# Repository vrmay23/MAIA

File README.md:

# MAIA
ADAS for blind dogs!

## Third-Party Dependencies

This project uses the VL53L5CX Ultra Lite Driver (ULD) from
STMicroelectronics, licensed under BSD-3-Clause.

The ULD is NOT included in this repository. It is downloaded
automatically at build time via the ESP-IDF Component Manager
using the manifest at `components/drivers/vl53l5cx/idf_component.yml`.

- Source: https://github.com/STMicroelectronics/stm32-vl53l5cx
- License: BSD-3-Clause, (c) STMicroelectronics

### Integration approach

The ST ULD provides the sensor core logic (`vl53l5cx_api.c`)
and expects the user to implement a platform layer (`platform.h`)
with I2C and delay callbacks.

MAIA provides its own `platform.h` and `vl53l5cx_platform.c`
using the ESP-IDF v6.0 new I2C master API. The ST `porting/`
directory is intentionally excluded from the build — only
`modules/vl53l5cx_api.c` is compiled from the ULD.

This keeps the repository 100% Apache 2.0 while the ST ULD
is consumed as an external dependency at build time.

## Building
idf.py build

The Component Manager downloads the ST ULD automatically.
No manual steps required.

## ⚠️ DISCLAIMER

THIS IS AN EXPERIMENTAL OPEN-SOURCE PROJECT FOR EDUCATIONAL
AND RESEARCH PURPOSES ONLY.

No Warranty of Operation: This ADAS system for blind dogs is
provided on an "AS IS" BASIS, without warranties or conditions
of any kind, either express or implied. ToF sensors are subject
to environmental interference, signal noise, blind spots, and
false negatives/positives.

Assumption of Risk: The use of this hardware and firmware on
animals is at the sole discretion and risk of the user/builder.
The author(s) shall not be held liable for any collisions,
injuries, property damage, or any other incidents resulting
from the use or failure of this device.

Not a Medical or Safety Device: This project is NOT a certified
medical or assistive device. It is not a substitute for human
supervision, professional veterinary advice, or proper
orientation training for visually impaired animals.

Hardware Safety: The builder is responsible for ensuring
electrical safety (battery insulation, thermal management) and
mechanical integrity (secure attachment to the animal) to
prevent risks of shock, fire, or physical harm.

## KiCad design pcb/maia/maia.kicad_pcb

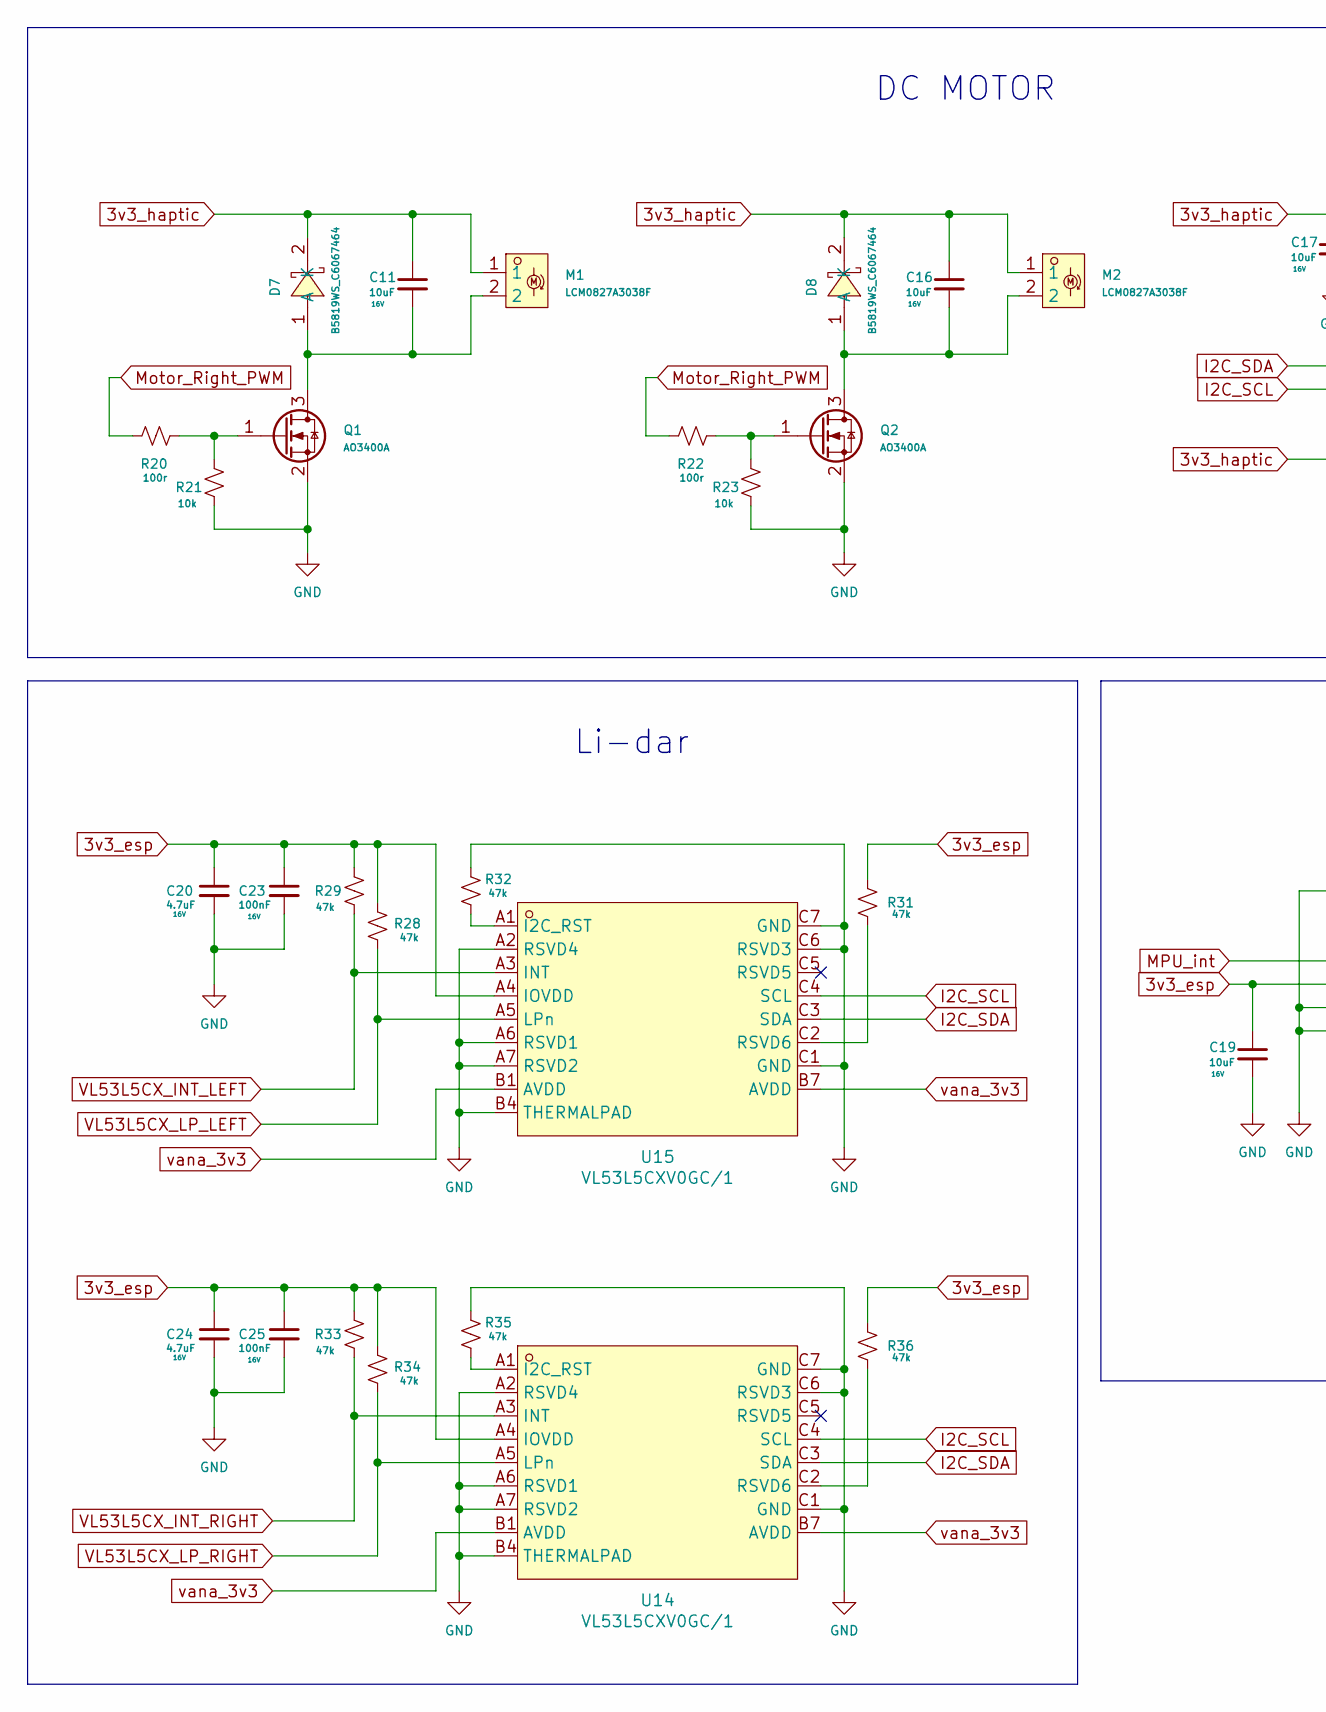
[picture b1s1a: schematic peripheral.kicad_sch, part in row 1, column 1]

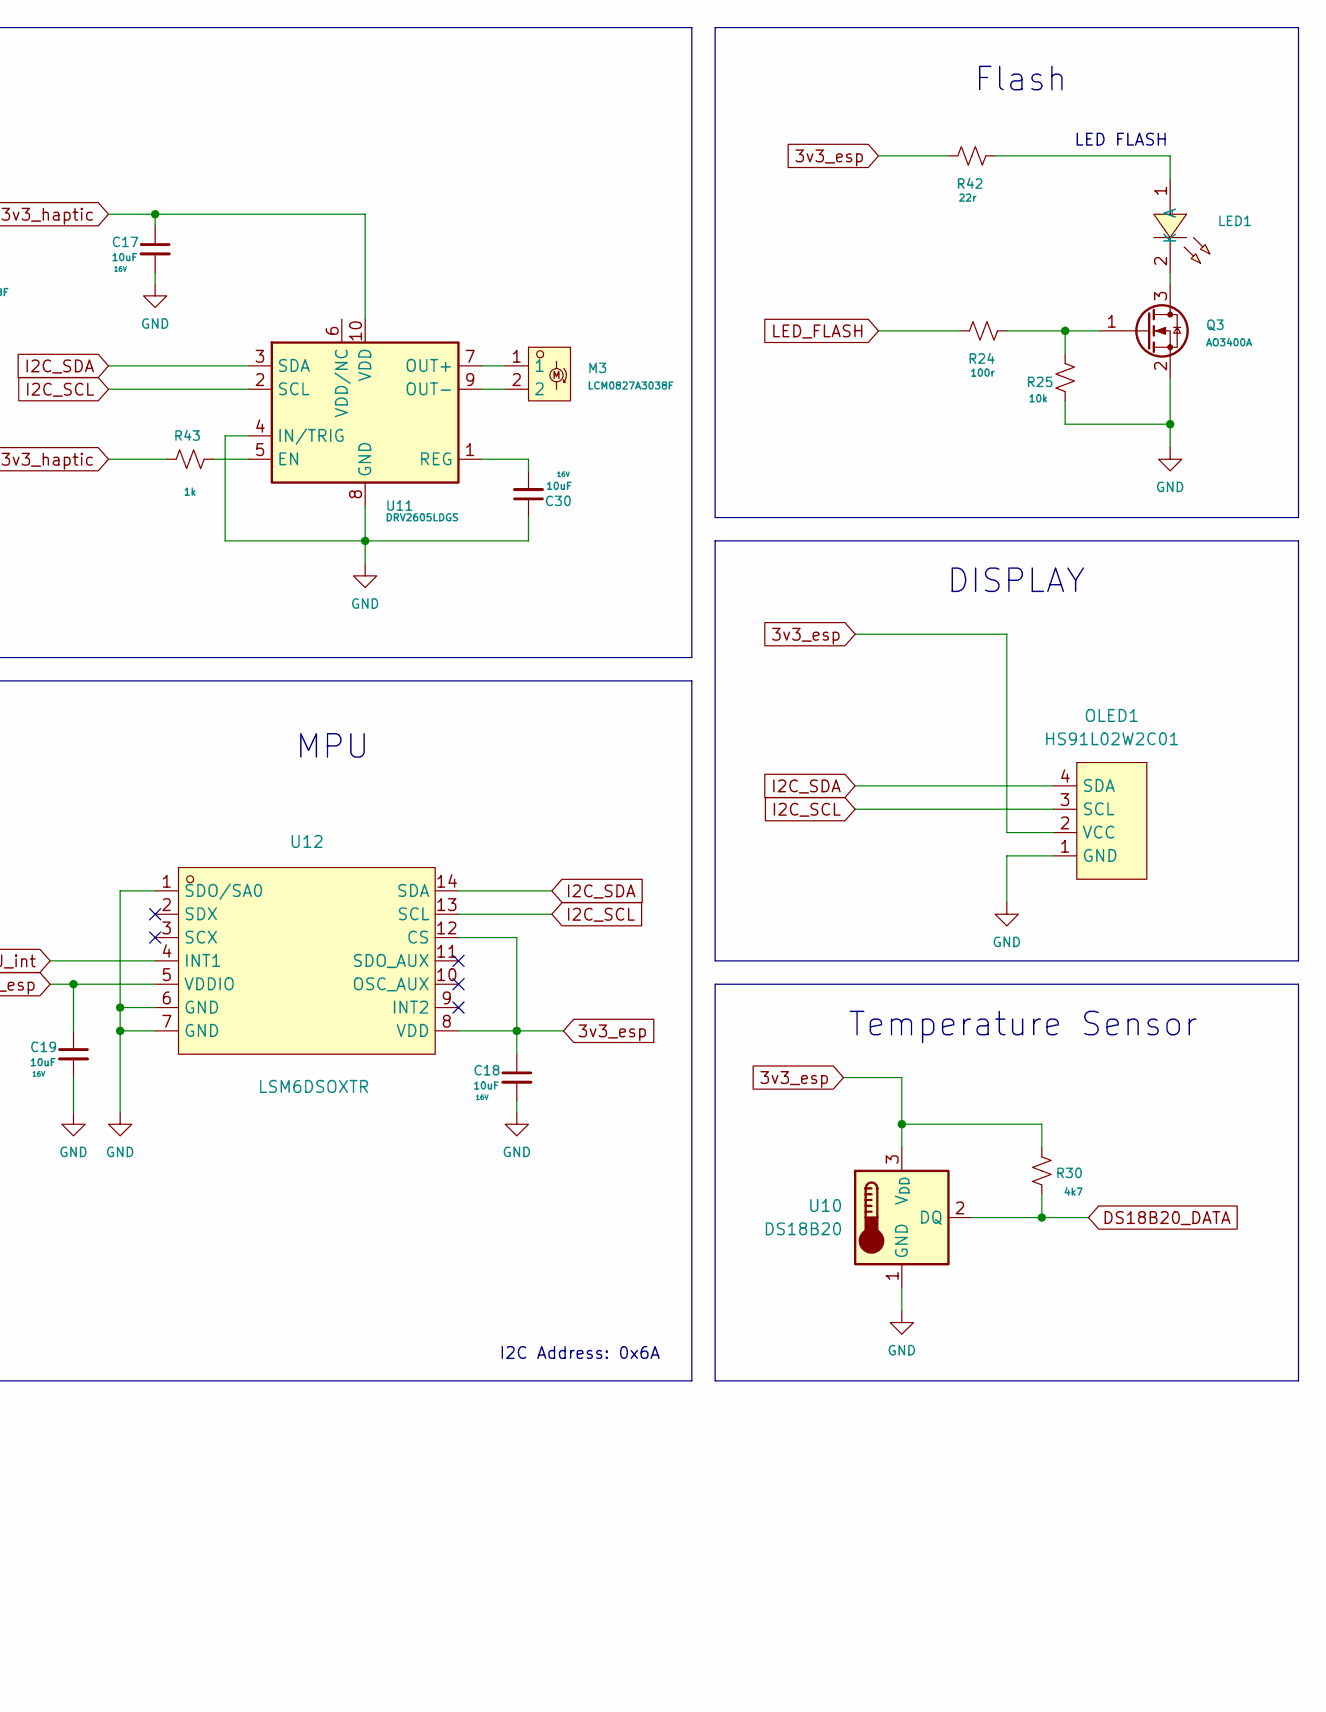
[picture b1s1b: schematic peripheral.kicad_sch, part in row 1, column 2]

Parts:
C11, C16, C17, C18, C19, C30: 10uF; C_0402_1005Metric; Voltage 16V; Tolerance 10%
C20, C24: 4.7uF; C_0402_1005Metric; Voltage 16V; Tolerance 10%
C23, C25: 100nF; C_0402_1005Metric; Voltage 16V; Tolerance 10%
D7, D8: B5819WS_C6067464; SOD-323F_L1.7-W1.3-LS2.5-R-RD-1; MPN B5819WS; LCSC Part C6067464
LED1: XL-3030WWC-1W-3V; LED-SMD_L3.0-W3.0_WHITE; MPN XL-3030WWC-1W-3V; LCSC Part C2843893
M1, M2, M3: LCM0827A3038F; VIBRATIONMOTOR-TH_LCM0827A3038F; MPN LCM0827A3038F; LCSC Part C2759981
OLED1: HS91L02W2C01; OLED-TH_L38.0-W12.0_HS91L02W2C01; MPN HS91L02W2C01; LCSC Part C5248081
Q1, Q2, Q3: AO3400A; SOT-23
R20, R22, R24: 100r; R_0603_1608Metric
R21, R23, R25: 10k; R_0603_1608Metric
R28, R29, R31, R32, R33, R34, R35, R36: 47k; R_0603_1608Metric
R30: 4k7; R_0603_1608Metric
R42: 22r; R_0603_1608Metric
R43: 1k; R_0603_1608Metric
U10: DS18B20; TO-92_Inline
U11: DRV2605LDGS; TSSOP-10_3x3mm_P0.5mm
U12: LSM6DSOXTR; LGA-14L_L3.0-W2.5-P0.50-TL; MPN LSM6DSOXTR; LCSC Part C481766
U14, U15: VL53L5CXV0GC/1; LGA-16_L6.4-W3.0_VL53L5CXV0GC-1; MPN VL53L5CXV0GC/1; LCSC Part C3178303

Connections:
3v3_esp: C18.1, C19.1, C20.1, C23.1, C24.1, C25.1, OLED1.2 (VCC), R28.2, R29.2, R30.2, R31.1, R33.2, R34.2, R36.1, R42.1, U10.3 (V_{DD}), U12.5 (VDDIO), U12.8 (VDD), U12.12 (CS), U14.A4 (IOVDD), U15.A4 (IOVDD); also elsewhere on the board
3v3_haptic: C11.1, C16.1, C17.1, D7.2 (K), D8.2 (K), M1.1, M2.1, R43.2, U11.10 (VDD); also elsewhere on the board
DS18B20_DATA: R30.1, U10.2 (DQ); also elsewhere on the board
GND: C17.2, C18.2, C19.2, C20.2, C23.2, C24.2, C25.2, C30.1, OLED1.1 (GND), Q1.2 (S), Q2.2 (S), Q3.2 (S), R21.2, R23.2, R25.2, R32.2, R35.2, U10.1 (GND), U11.4 (IN/TRIG), U11.8 (GND), U12.1 (SDO/SA0), U12.6 (GND), U12.7 (GND), U14.A2 (RSVD4), U14.A6 (RSVD1), U14.A7 (RSVD2), U14.B4 (THERMALPAD), U14.C1 (GND), U14.C6 (RSVD3), U14.C7 (GND), U15.A2 (RSVD4), U15.A6 (RSVD1), U15.A7 (RSVD2), U15.B4 (THERMALPAD), U15.C1 (GND), U15.C6 (RSVD3), U15.C7 (GND); also elsewhere on the board
I2C_SCL: OLED1.3 (SCL), U11.2 (SCL), U12.13 (SCL), U14.C4 (SCL), U15.C4 (SCL); also elsewhere on the board
I2C_SDA: OLED1.4 (SDA), U11.3 (SDA), U12.14 (SDA), U14.C3 (SDA), U15.C3 (SDA); also elsewhere on the board
LED_FLASH: R24.1; also elsewhere on the board
MPU_int: U12.4 (INT1); also elsewhere on the board
Motor_Right_PWM: R20.1, R22.1; also elsewhere on the board
unnamed: C11.2, D7.1 (A), M1.2, Q1.3 (D)
unnamed: C16.2, D8.1 (A), M2.2, Q2.3 (D)
unnamed: LED1.1 (A), R42.2
unnamed: LED1.2 (K), Q3.3 (D)
unnamed: Q1.1 (G), R20.2, R21.1
unnamed: Q2.1 (G), R22.2, R23.1
unnamed: Q3.1 (G), R24.2, R25.1
unnamed: R43.1, U11.5 (EN)
unnamed: M3.1, U11.7 (OUT+)
unnamed: M3.2, U11.9 (OUT-)
unnamed: C30.2, U11.1 (REG)
unnamed: R35.1, U14.A1 (I2C_RST)
unnamed: R36.2, U14.C2 (RSVD6)
unnamed: R32.1, U15.A1 (I2C_RST)
unnamed: R31.2, U15.C2 (RSVD6)
VL53L5CX_INT_LEFT: R29.1, U15.A3 (INT); also elsewhere on the board
VL53L5CX_INT_RIGHT: R33.1, U14.A3 (INT); also elsewhere on the board
VL53L5CX_LP_LEFT: R28.1, U15.A5 (LPn); also elsewhere on the board
VL53L5CX_LP_RIGHT: R34.1, U14.A5 (LPn); also elsewhere on the board
vana_3v3: U14.B1 (AVDD), U14.B7 (AVDD), U15.B1 (AVDD), U15.B7 (AVDD); also elsewhere on the board

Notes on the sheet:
DC MOTOR
DISPLAY
Temperature Sensor
Li-dar
MPU
LED FLASH
Flash
I2C Address: 0x6A

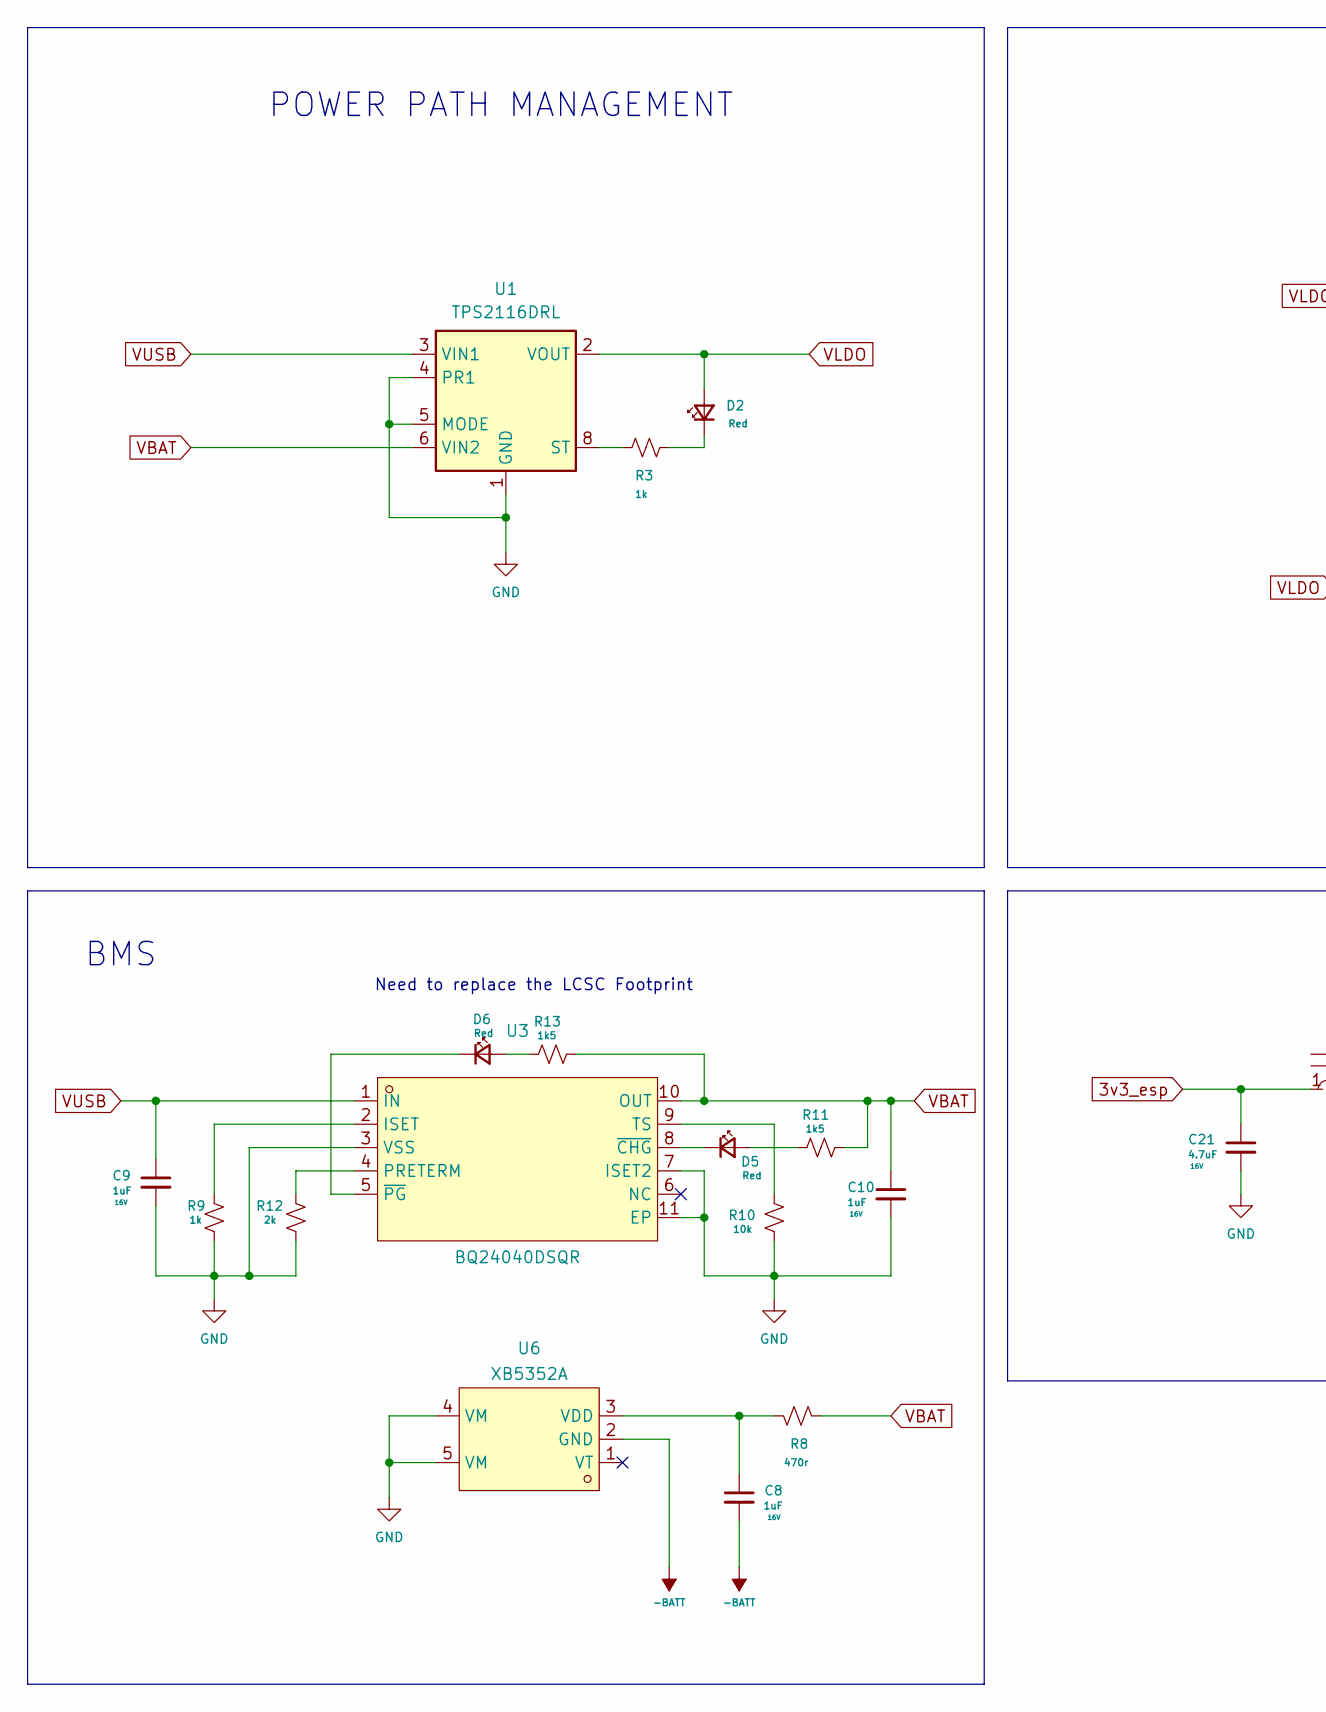
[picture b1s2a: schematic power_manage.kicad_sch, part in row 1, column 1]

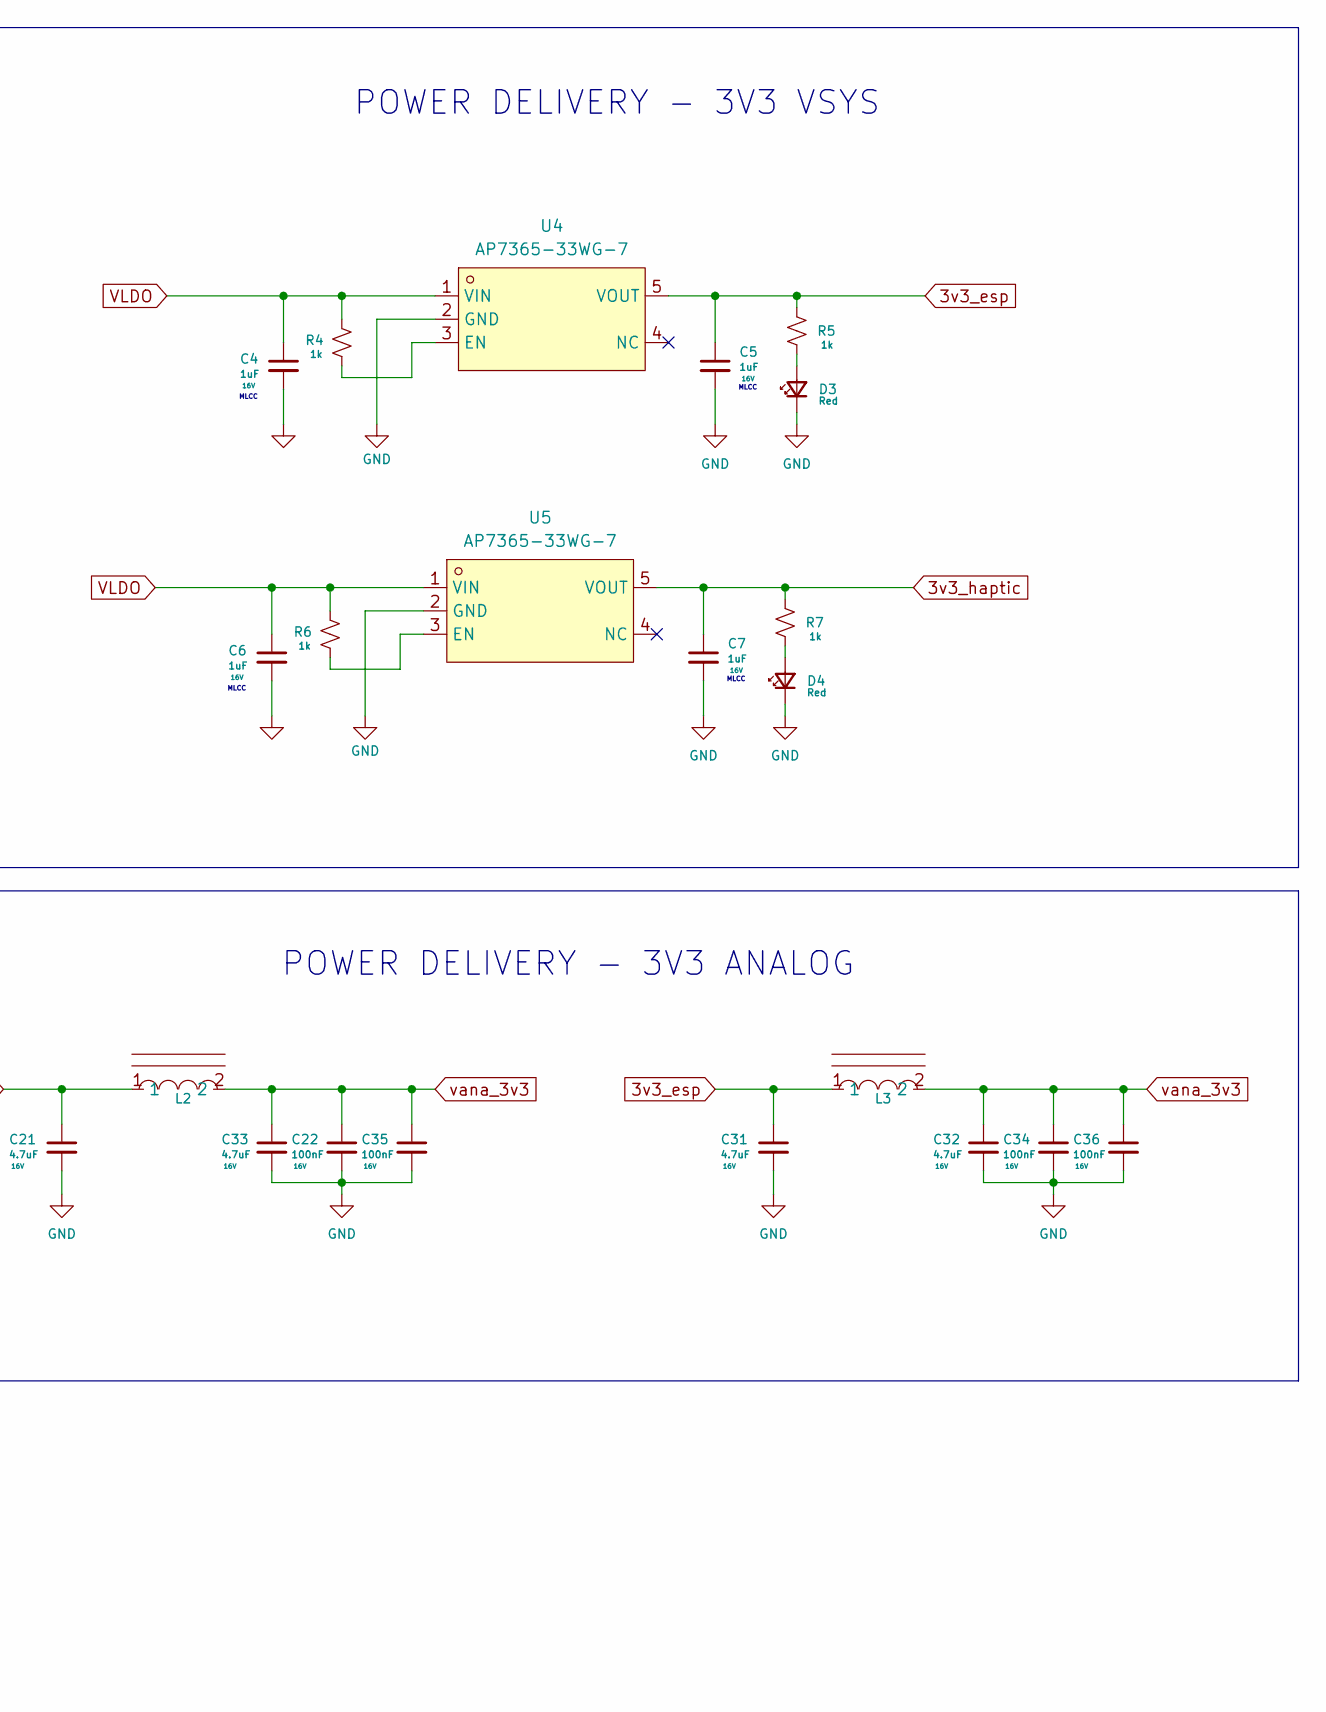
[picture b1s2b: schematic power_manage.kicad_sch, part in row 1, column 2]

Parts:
C4, C5, C6, C7, C8, C9, C10: 1uF; C_0402_1005Metric; Voltage 16V; Tolerance 10%
C21, C31, C32, C33: 4.7uF; C_0402_1005Metric; Voltage 16V; Tolerance 10%
C22, C34, C35, C36: 100nF; C_0402_1005Metric; Voltage 16V; Tolerance 10%
D2, D3, D4, D5, D6: Red; LED_0603_1608Metric_Red
L2, L3: HCB3216KF-601T30; L1206; MPN HCB3216KF-601T30; LCSC Part C357023
R3, R4, R5, R6, R7, R9: 1k; R_0603_1608Metric
R8: 470r; R_0603_1608Metric
R10: 10k; R_0603_1608Metric
R11, R13: 1k5; R_0603_1608Metric
R12: 2k; R_0603_1608Metric
U1: TPS2116DRL; SOT-583-8
U3: BQ24040DSQR; WSON-10_L2.0-W2.0-P0.40-BL-EP; MPN BQ24040DSQR; LCSC Part C81080
U4, U5: AP7365-33WG-7; SOT-25_L3.0-W1.6-P0.95-LS2.8-BR; MPN AP7365-33WG-7; LCSC Part C150742
U6: XB5352A; SOT-23-5_L3.0-W1.7-P0.95-LS2.8-BR; MPN XB5352A; LCSC Part C154943

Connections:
3v3_esp: C5.1, C21.1, C31.1, L2.1, L3.1, R5.2, U4.5 (VOUT); also elsewhere on the board
3v3_haptic: C7.1, R7.2, U5.5 (VOUT); also elsewhere on the board
-BATT: C8.2, U6.2 (GND); also elsewhere on the board
GND: C4.2, C5.2, C6.2, C7.2, C9.2, C10.2, C21.2, C22.2, C31.2, C32.2, C33.2, C34.2, C35.2, C36.2, D3.1 (K), D4.1 (K), R9.2, R10.2, R12.1, U1.1 (GND), U1.4 (PR1), U1.5 (MODE), U3.3 (VSS), U3.7 (ISET2), U3.11 (EP), U4.2 (GND), U5.2 (GND), U6.4 (VM), U6.5 (VM); also elsewhere on the board
unnamed: D2.1 (K), R3.2
unnamed: D3.2 (A), R5.1
unnamed: D4.2 (A), R7.1
unnamed: D5.2 (A), R11.2
unnamed: D5.1 (K), U3.8 (~CHG)
unnamed: D6.2 (A), R13.2
unnamed: D6.1 (K), U3.5 (~PG)
unnamed: R3.1, U1.8 (ST)
unnamed: R9.1, U3.2 (ISET)
unnamed: R12.2, U3.4 (PRETERM)
unnamed: R10.1, U3.9 (TS)
unnamed: R4.2, U4.3 (EN)
unnamed: R6.2, U5.3 (EN)
unnamed: C8.1, R8.2, U6.3 (VDD)
VBAT: C10.1, R8.1, R11.1, R13.1, U1.6 (VIN2), U3.10 (OUT); also elsewhere on the board
VLDO: C4.1, C6.1, D2.2 (A), R4.1, R6.1, U1.2 (VOUT), U1.7 (VOUT), U4.1 (VIN), U5.1 (VIN)
VUSB: C9.1, U1.3 (VIN1), U3.1 (IN); also elsewhere on the board
vana_3v3: C22.1, C32.1, C33.1, C34.1, C35.1, C36.1, L2.2, L3.2; also elsewhere on the board

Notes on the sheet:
MLCC
POWER PATH MANAGEMENT
Need to replace the LCSC Footprint
POWER DELIVERY - 3V3 VSYS
POWER DELIVERY - 3V3 ANALOG
BMS

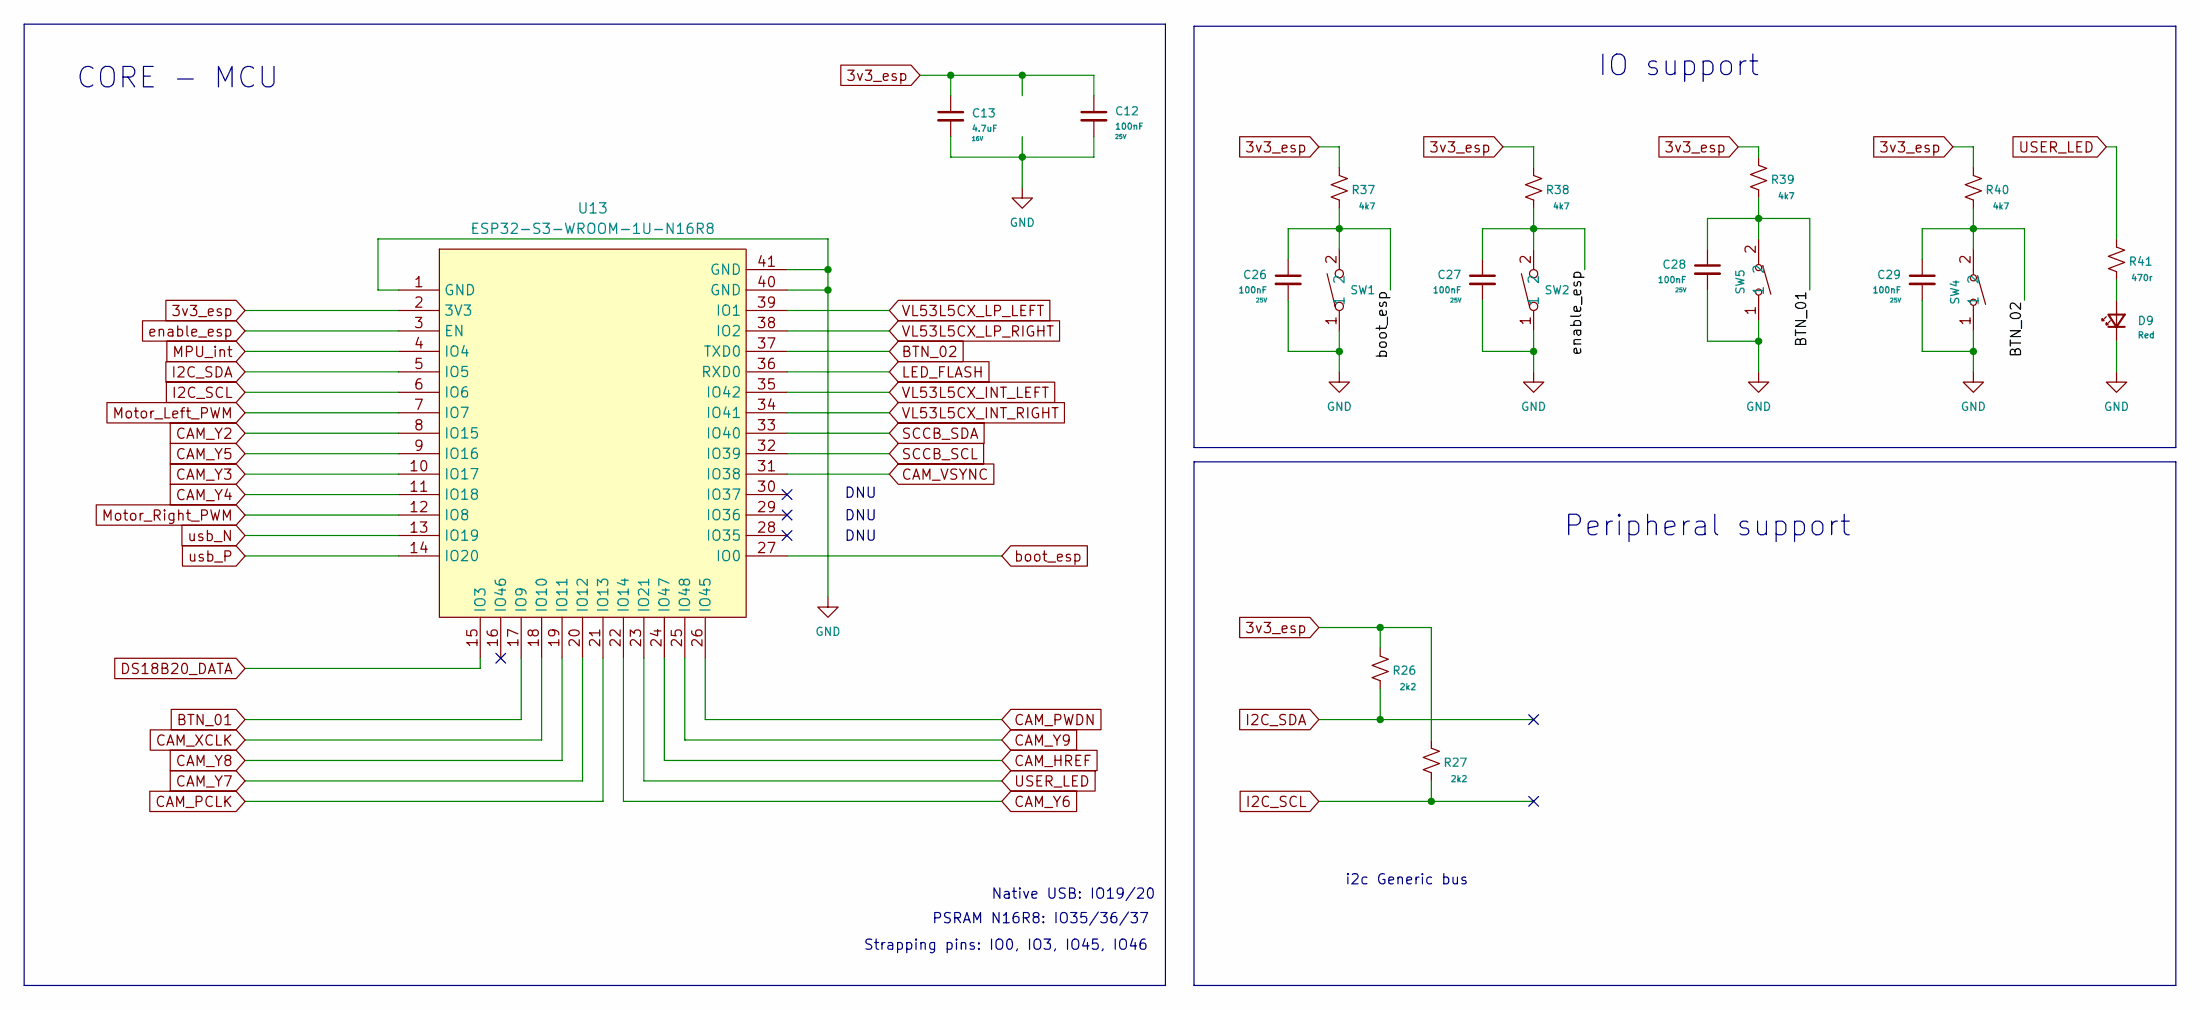
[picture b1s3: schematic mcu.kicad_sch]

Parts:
C12, C26, C27, C28, C29: 100nF; C_0402_1005Metric; Voltage 25V; Tolerance 10%
C13: 4.7uF; C_0402_1005Metric; Voltage 16V; Tolerance 10%
D9: Red; LED_0603_1608Metric_Red
R26, R27: 2k2; R_0603_1608Metric
R37, R38, R39, R40: 4k7; R_0603_1608Metric
R41: 470r; R_0603_1608Metric
SW1, SW2: HX 3X4X2-2P-1.6N TACTILE SWITCH; KEY-SMD_L4.0-W3.0-LS4.9-1; MPN HX 3x4x2-2P-1.6N TACTILE SWITCH; LCSC Part C49234124
SW4, SW5: TS-KG01T-ACT50F; SW-SMD_L6.0-W3.5-LS8.0-EH; MPN TS-KG01T-ACT50F; LCSC Part C2874211
U13: ESP32-S3-WROOM-1U-N16R8; WIRELM-SMD_ESP32-S3-WROOM-1U; MPN ESP32-S3-WROOM-1U-N16R8; LCSC Part C3013946

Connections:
3v3_esp: C12.1, C13.1, R26.2, R27.2, R37.2, R38.2, R39.2, R40.2, U13.2 (3V3); also elsewhere on the board
BTN_01: C28.1, R39.1, SW5.2, U13.17 (IO9)
BTN_02: C29.1, R40.1, SW4.2, U13.37 (TXD0)
CAM_HREF: U13.24 (IO47); also elsewhere on the board
CAM_PCLK: U13.21 (IO13); also elsewhere on the board
CAM_PWDN: U13.26 (IO45); also elsewhere on the board
CAM_VSYNC: U13.31 (IO38); also elsewhere on the board
CAM_XCLK: U13.18 (IO10); also elsewhere on the board
CAM_Y2: U13.8 (IO15); also elsewhere on the board
CAM_Y3: U13.10 (IO17); also elsewhere on the board
CAM_Y4: U13.11 (IO18); also elsewhere on the board
CAM_Y5: U13.9 (IO16); also elsewhere on the board
CAM_Y6: U13.22 (IO14); also elsewhere on the board
CAM_Y7: U13.20 (IO12); also elsewhere on the board
CAM_Y8: U13.19 (IO11); also elsewhere on the board
CAM_Y9: U13.25 (IO48); also elsewhere on the board
DS18B20_DATA: U13.15 (IO3); also elsewhere on the board
GND: C12.2, C13.2, C26.2, C27.2, C28.2, C29.2, D9.1 (K), SW1.1, SW2.1, SW4.1, SW5.1, U13.1 (GND), U13.40 (GND), U13.41 (GND); also elsewhere on the board
I2C_SCL: R27.1, U13.6 (IO6); also elsewhere on the board
I2C_SDA: R26.1, U13.5 (IO5); also elsewhere on the board
LED_FLASH: U13.36 (RXD0); also elsewhere on the board
MPU_int: U13.4 (IO4); also elsewhere on the board
Motor_Left_PWM: U13.7 (IO7)
Motor_Right_PWM: U13.12 (IO8); also elsewhere on the board
unnamed: D9.2 (A), R41.1
SCCB_SCL: U13.32 (IO39); also elsewhere on the board
SCCB_SDA: U13.33 (IO40); also elsewhere on the board
USER_LED: R41.2, U13.23 (IO21)
VL53L5CX_INT_LEFT: U13.35 (IO42); also elsewhere on the board
VL53L5CX_INT_RIGHT: U13.34 (IO41); also elsewhere on the board
VL53L5CX_LP_LEFT: U13.39 (IO1); also elsewhere on the board
VL53L5CX_LP_RIGHT: U13.38 (IO2); also elsewhere on the board
boot_esp: C26.1, R37.1, SW1.2, U13.27 (IO0)
enable_esp: C27.1, R38.1, SW2.2, U13.3 (EN)
usb_N: U13.13 (IO19); also elsewhere on the board
usb_P: U13.14 (IO20); also elsewhere on the board

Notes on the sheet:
i2c Generic bus
Native USB: IO19/20
DNU
IO support
PSRAM N16R8: IO35/36/37
Strapping pins: IO0, IO3, IO45, IO46
CORE - MCU
Peripheral support

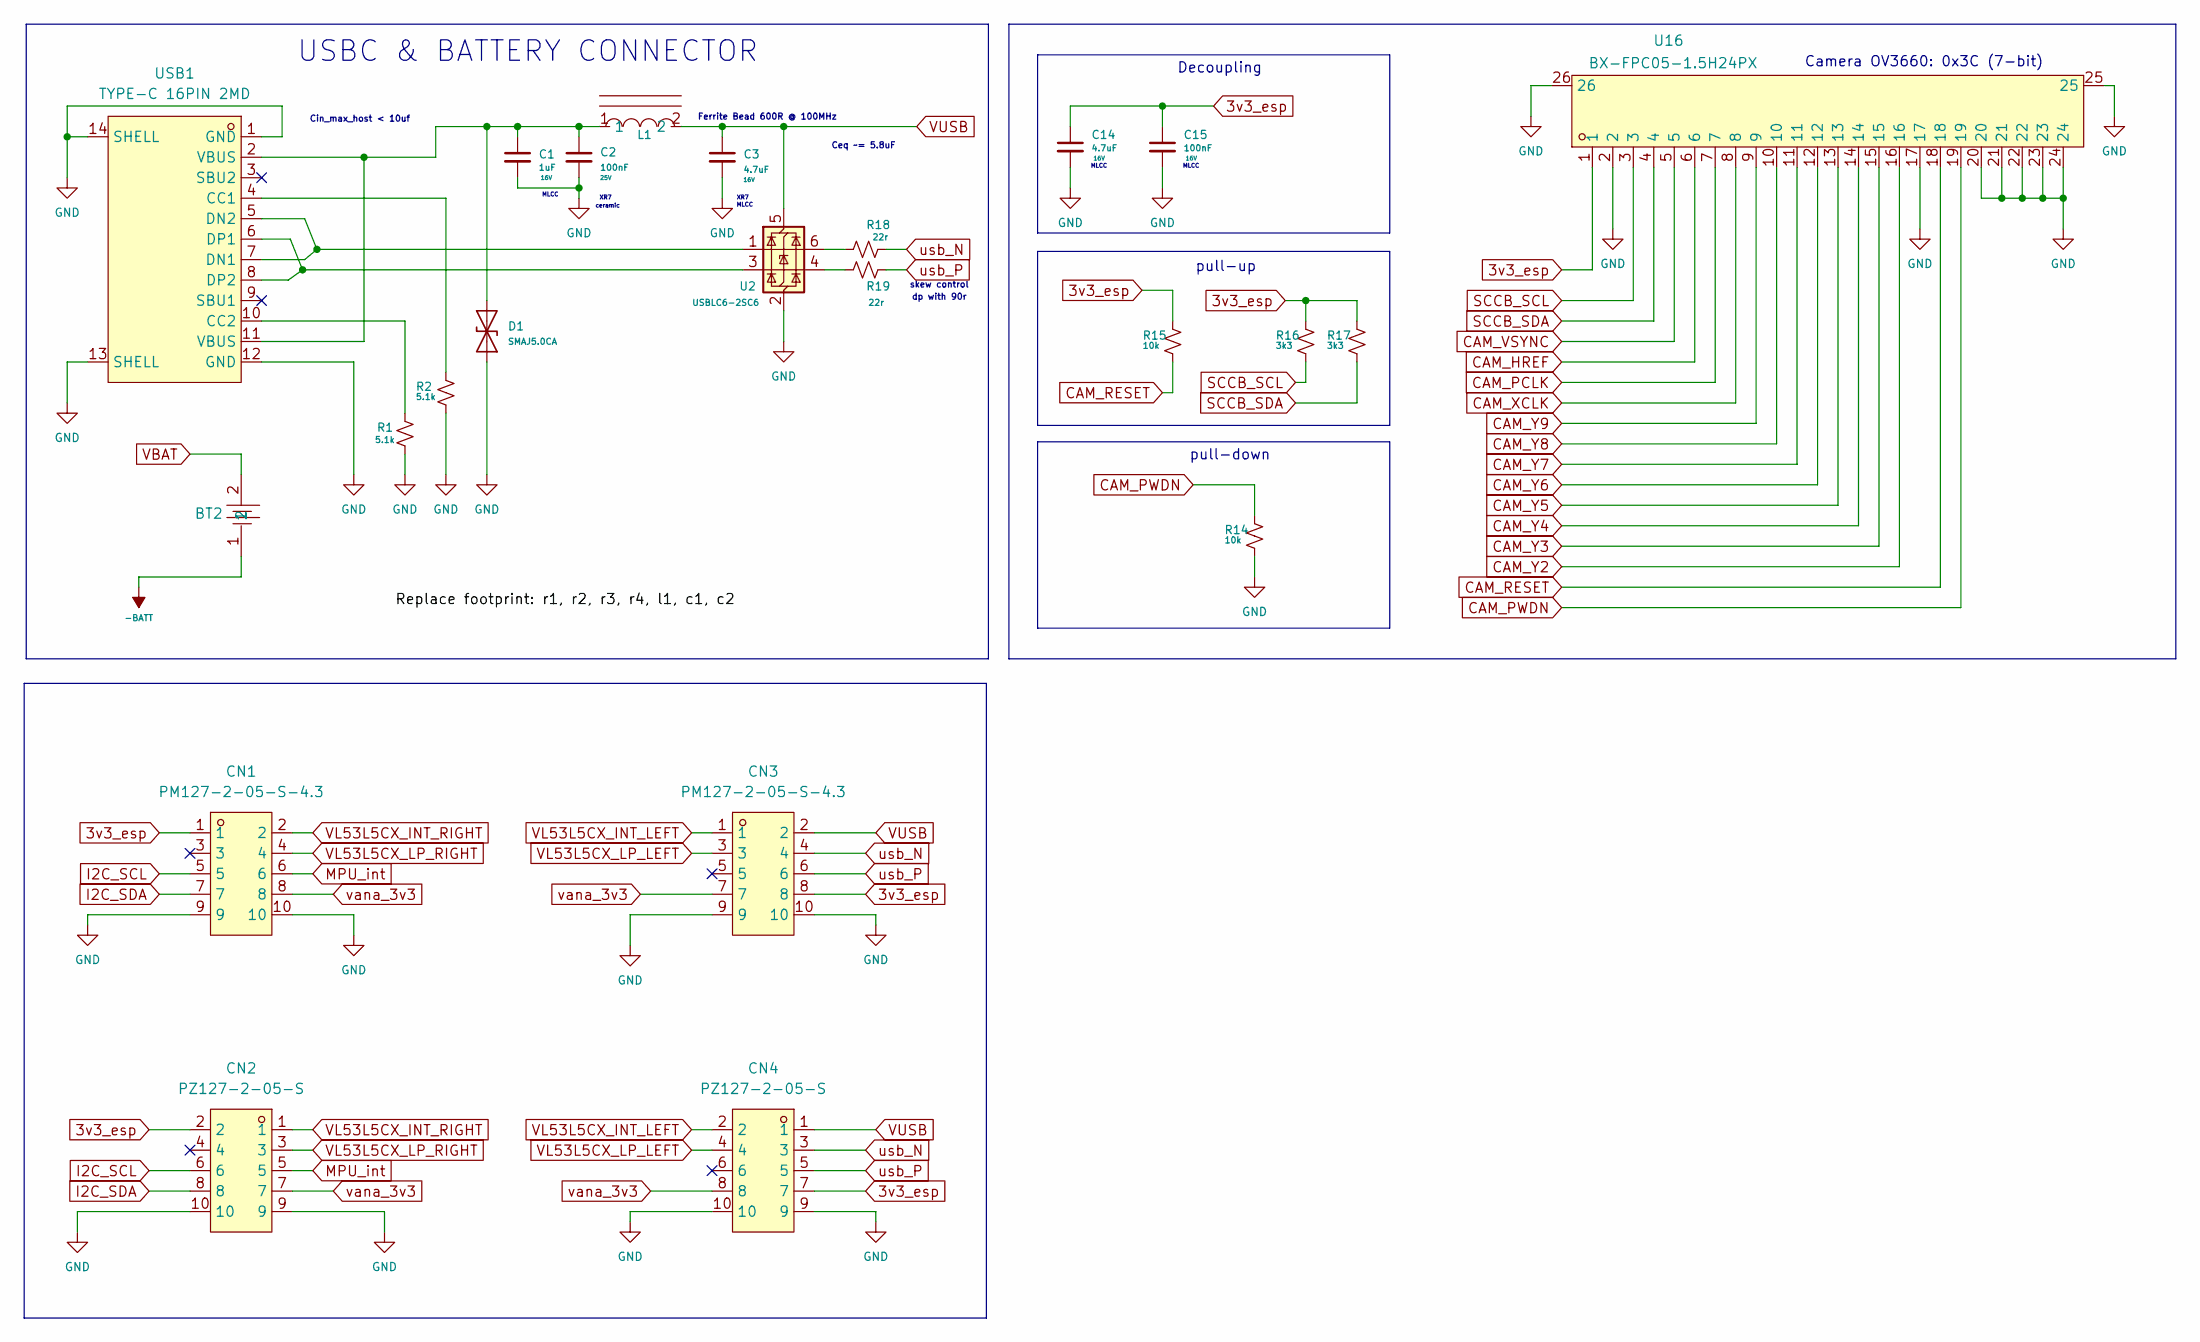
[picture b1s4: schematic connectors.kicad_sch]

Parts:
BT2: BH-18650-B1BA002; BATTERY-SMD_18650-1S-L77.1-W20.7-1; MPN BH-18650-B1BA002; LCSC Part C2988620
C1: 1uF; C_0402_1005Metric; Voltage 16V; Tolerance 10%
C2: 100nF; C_0402_1005Metric; Voltage 25V; Tolerance 10%
C3, C14: 4.7uF; C_0402_1005Metric; Voltage 16V; Tolerance 10%
C15: 100nF; C_0402_1005Metric; Voltage 16V; Tolerance 10%
CN1, CN3: PM127-2-05-S-4.3; HDR-SMD_10P-P1.27-V-F-R2-C5-LS4.8; MPN PM127-2-05-S-4.3; LCSC Part C3975131
CN2, CN4: PZ127-2-05-S; HDR-SMD_10P-P1.27-V-M-R2-C5-LS5.3; MPN PZ127-2-05-S; LCSC Part C3975188
D1: SMAJ5.0CA; D_SMA
L1: HCB3216KF-601T30; L1206; MPN HCB3216KF-601T30; LCSC Part C357023
R1, R2: 5.1k; R_0603_1608Metric
R14, R15: 10k; R_0603_1608Metric
R16, R17: 3k3; R_0603_1608Metric
R18, R19: 22r; R_0603_1608Metric
U2: USBLC6-2SC6; SOT-23-6
U16: BX-FPC05-1.5H24PX; FPC-SMD_24P-P0.50_BX-FPC05-1.5H24PX; MPN BX-FPC05-1.5H24PX; LCSC Part C18078354
USB1: TYPE-C 16PIN 2MD; USB-C-SMD_TYPE-C-6PIN-2MD-073; MPN TYPE-C 16PIN 2MD(073); LCSC Part C2765186

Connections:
3v3_esp: C14.1, C15.1, CN1.1, CN2.2, CN3.8, CN4.7, R15.1, R16.1, R17.1, U16.1; also elsewhere on the board
-BATT: BT2.1; also elsewhere on the board
CAM_HREF: U16.6; also elsewhere on the board
CAM_PCLK: U16.7; also elsewhere on the board
CAM_PWDN: R14.1, U16.19; also elsewhere on the board
CAM_RESET: R15.2, U16.18
CAM_VSYNC: U16.5; also elsewhere on the board
CAM_XCLK: U16.8; also elsewhere on the board
CAM_Y2: U16.16; also elsewhere on the board
CAM_Y3: U16.15; also elsewhere on the board
CAM_Y4: U16.14; also elsewhere on the board
CAM_Y5: U16.13; also elsewhere on the board
CAM_Y6: U16.12; also elsewhere on the board
CAM_Y7: U16.11; also elsewhere on the board
CAM_Y8: U16.10; also elsewhere on the board
CAM_Y9: U16.9; also elsewhere on the board
GND: C1.2, C2.2, C3.2, C14.2, C15.2, CN1.9, CN1.10, CN2.9, CN2.10, CN3.9, CN3.10, CN4.9, CN4.10, D1.1 (A1), R1.2, R2.2, R14.2, U2.2 (GND), U16.2, U16.17, U16.20, U16.21, U16.22, U16.23, U16.24, U16.25, U16.26, USB1.1 (GND), USB1.12 (GND), USB1.13 (SHELL), USB1.14 (SHELL); also elsewhere on the board
I2C_SCL: CN1.5, CN2.6; also elsewhere on the board
I2C_SDA: CN1.7, CN2.8; also elsewhere on the board
MPU_int: CN1.6, CN2.5; also elsewhere on the board
unnamed: C1.1, C2.1, D1.2 (A2), L1.1, USB1.2 (VBUS), USB1.11 (VBUS)
unnamed: R18.1, U2.6 (I/O1)
unnamed: R19.1, U2.4 (I/O2)
unnamed: R2.1, USB1.4 (CC1)
unnamed: R1.1, USB1.10 (CC2)
unnamed: U2.1 (I/O1), USB1.5 (DN2), USB1.7 (DN1)
unnamed: U2.3 (I/O2), USB1.6 (DP1), USB1.8 (DP2)
SCCB_SCL: R16.2, U16.3; also elsewhere on the board
SCCB_SDA: R17.2, U16.4; also elsewhere on the board
VBAT: BT2.2; also elsewhere on the board
VL53L5CX_INT_LEFT: CN3.1, CN4.2; also elsewhere on the board
VL53L5CX_INT_RIGHT: CN1.2, CN2.1; also elsewhere on the board
VL53L5CX_LP_LEFT: CN3.3, CN4.4; also elsewhere on the board
VL53L5CX_LP_RIGHT: CN1.4, CN2.3; also elsewhere on the board
VUSB: C3.1, CN3.2, CN4.1, L1.2, U2.5 (VBUS); also elsewhere on the board
usb_N: CN3.4, CN4.3, R18.2; also elsewhere on the board
usb_P: CN3.6, CN4.5, R19.2; also elsewhere on the board
vana_3v3: CN1.8, CN2.7, CN3.7, CN4.8; also elsewhere on the board

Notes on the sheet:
pull-up
ceramic
Cin_max_host < 10uf
Ferrite Bead 600R @ 100MHz
skew control
XR7
Camera OV3660: 0x3C (7-bit)
Ceq ~= 5.8uF
USBC & BATTERY CONNECTOR
pull-down
MLCC
dp with 90r
Decoupling

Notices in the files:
components/maia_board/include/maia_board.h:
Copyright 2026 Vinicius May
Licensed under the Apache License, Version 2.0 (the "License");
